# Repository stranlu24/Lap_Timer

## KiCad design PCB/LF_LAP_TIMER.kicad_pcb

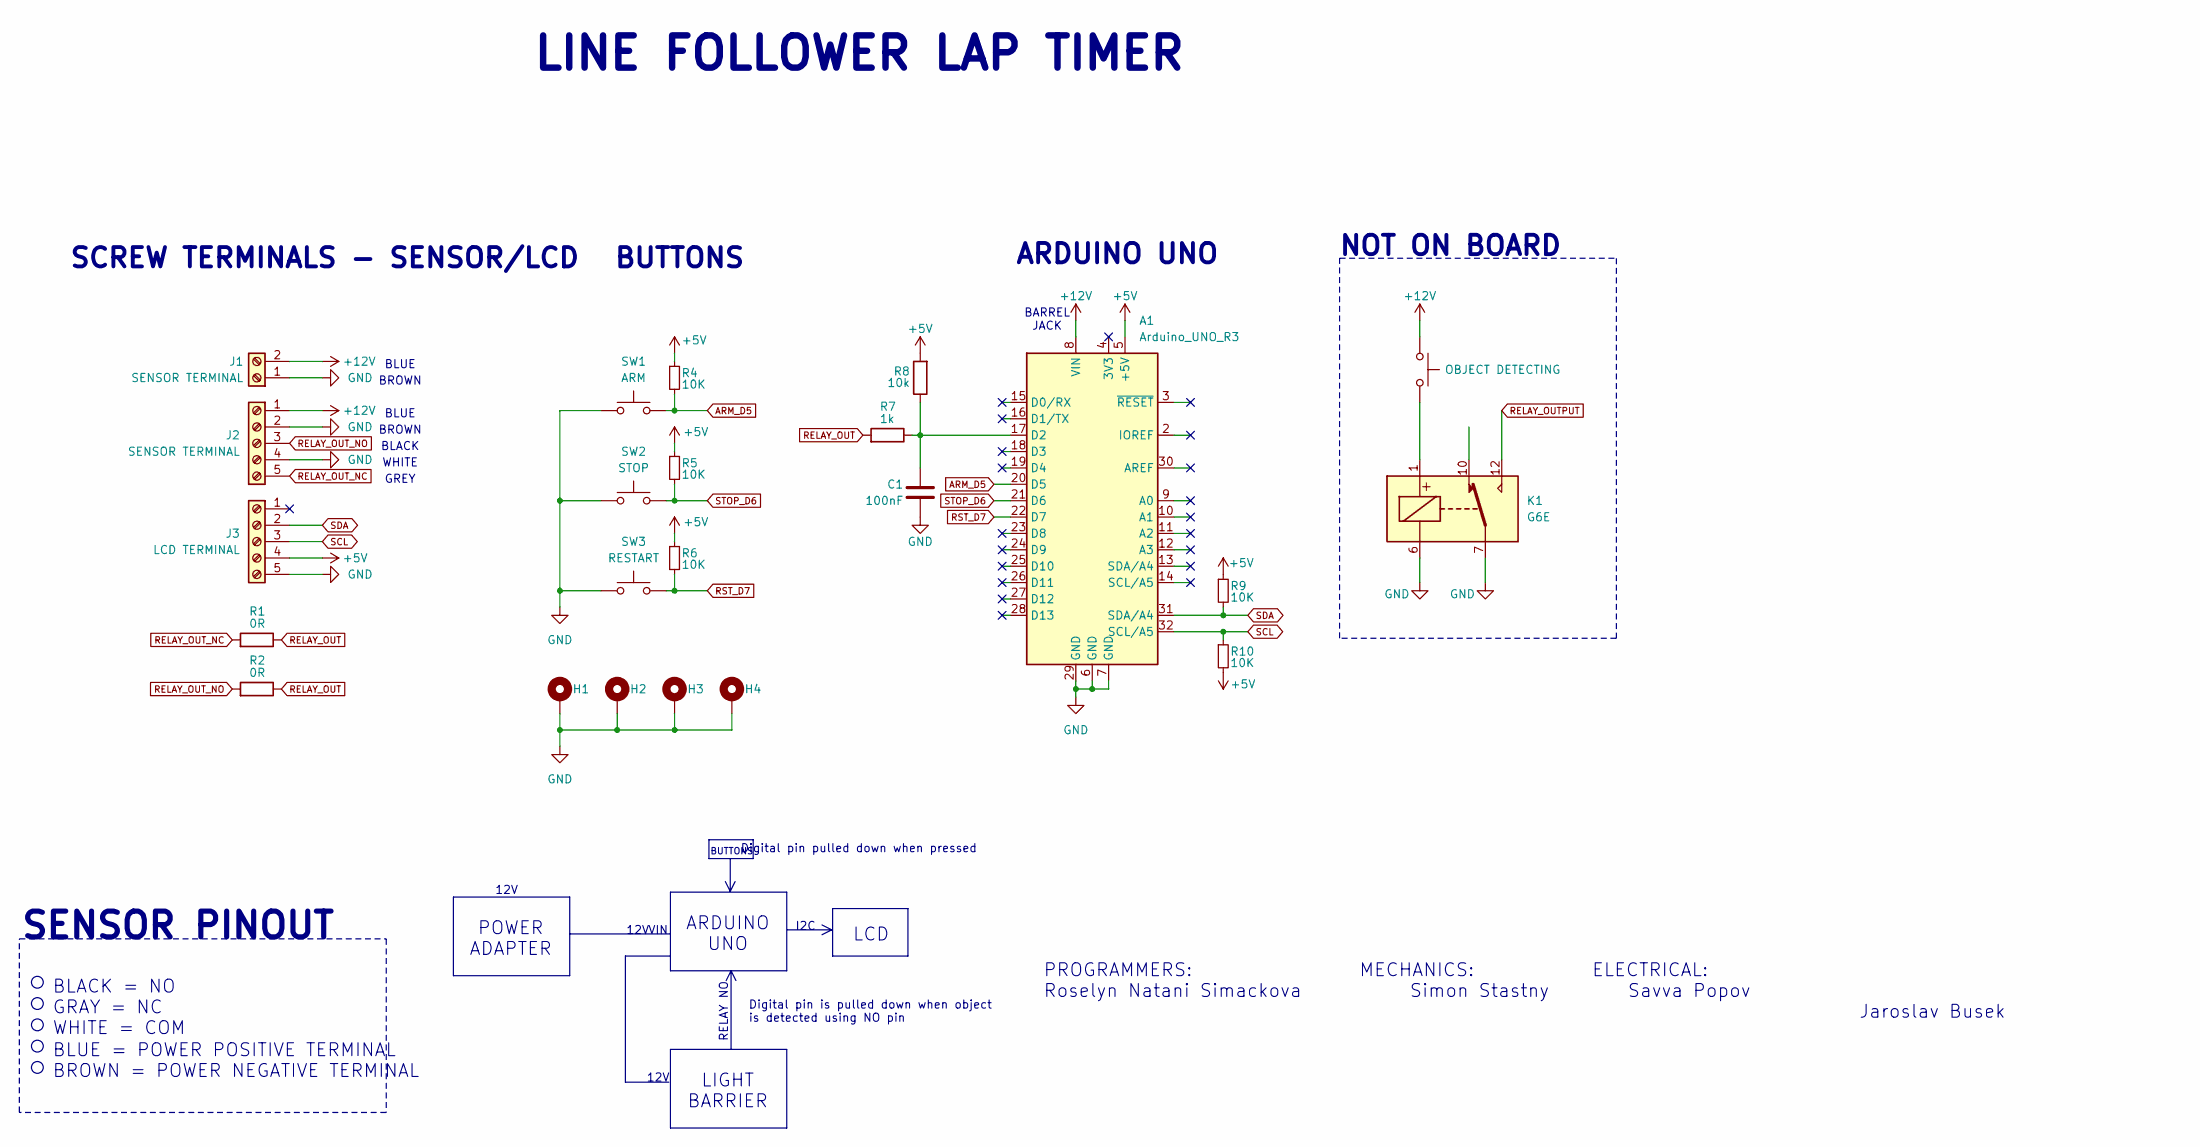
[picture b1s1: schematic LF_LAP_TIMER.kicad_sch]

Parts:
A1: Arduino_UNO_R3
C1: 100nF; C_Disc_D6.0mm_W2.5mm_P5.00mm
H1, H2, H3, H4: MountingHole_Pad; MountingHole_3.2mm_M3_Pad
J1: SENSOR TERMINAL; TerminalBlock_MaiXu_MX126-5.0-02P_1x02_P5.00mm
J2: SENSOR TERMINAL; TerminalBlock_MaiXu_MX126-5.0-05P_1x05_P5.00mm
J3: LCD TERMINAL; TerminalBlock_MaiXu_MX126-5.0-05P_1x05_P5.00mm
K1: G6E
R1, R2: 0R; R_Axial_DIN0207_L6.3mm_D2.5mm_P10.16mm_Horizontal
R4, R5, R6, R9, R10: 10K; R_Axial_DIN0207_L6.3mm_D2.5mm_P10.16mm_Horizontal
R7: 1k; R_Axial_DIN0207_L6.3mm_D2.5mm_P10.16mm_Horizontal
R8: 10k; R_Axial_DIN0207_L6.3mm_D2.5mm_P10.16mm_Horizontal
SW1: ARM; TerminalBlock_MaiXu_MX126-5.0-02P_1x02_P5.00mm
SW2: STOP; TerminalBlock_MaiXu_MX126-5.0-02P_1x02_P5.00mm
SW3: RESTART; TerminalBlock_MaiXu_MX126-5.0-02P_1x02_P5.00mm
SW4: OBJECT DETECTING

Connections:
+5V: A1.5 (+5V), J3.4, R4.1, R5.1, R6.1, R8.2, R9.1, R10.2
+12V: A1.8 (VIN), J1.2, J2.1, SW4.1
ARM_D5: A1.20 (D5), R4.2, SW1.2
GND: A1.6 (GND), A1.7 (GND), A1.29 (GND), C1.2, H1.1, H2.1, H3.1, H4.1, J1.1, J2.2, J2.4, J3.5, K1.6, K1.7, SW1.1, SW2.1, SW3.1
unnamed: A1.17 (D2), C1.1, R7.1, R8.1
unnamed: K1.1, SW4.2
RELAY_OUT: R1.1, R2.1, R7.2
RELAY_OUT_NC: J2.5, R1.2
RELAY_OUT_NO: J2.3, R2.2
RST_D7: A1.22 (D7), R6.2, SW3.2
SCL: A1.32 (SCL/A5), J3.3, R10.1
SDA: A1.31 (SDA/A4), J3.2, R9.2
STOP_D6: A1.21 (D6), R5.2, SW2.2

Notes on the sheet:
BLUE = POWER POSITIVE TERMINAL BROWN = POWER NEGATIVE TERMINAL
ARDUINO UNO
BROWN
BUTTONS
12V
SCREW TERMINALS - SENSOR/LCD
VIN
I2C
SENSOR PINOUT
BARREL JACK
RELAY NO
BLUE
WHITE
LIGHT BARRIER
BLACK
GREY
ARDUINO UNO
LINE FOLLOWER LAP TIMER
LCD
BLACK = NO GRAY = NC WHITE = COM
POWER ADAPTER
NOT ON BOARD
Digital pin pulled down when pressed
PROGRAMMERS: MECHANICS: ELECTRICAL: Roselyn Natani Simackova Simon Stastny Savva Popov Jaroslav Busek
Digital pin is pulled down when object is detected using NO pin

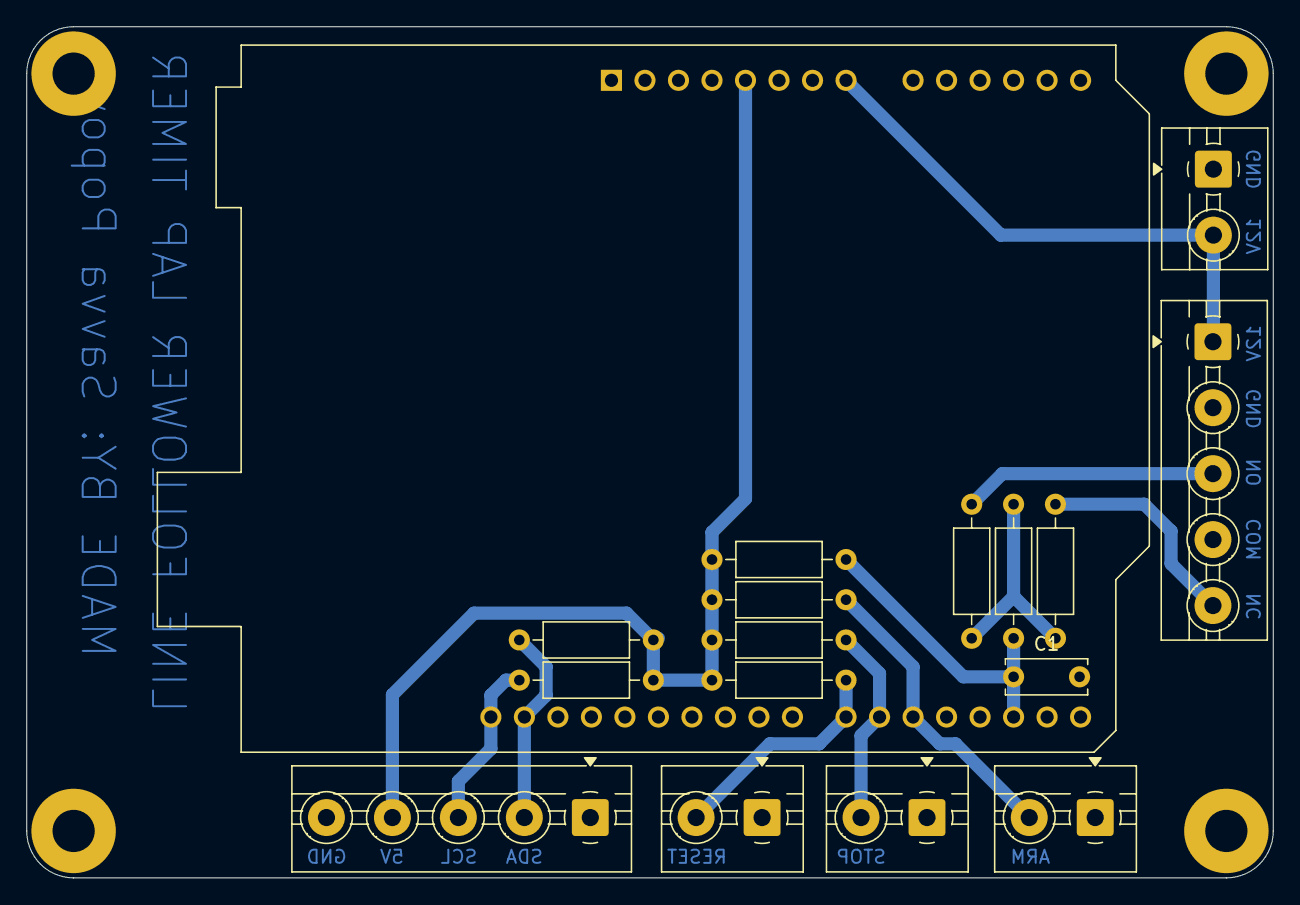
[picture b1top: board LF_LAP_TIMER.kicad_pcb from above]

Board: 2 copper layers, 94.5 x 64.5 mm, 21 parts (0 on the bottom side), 12 nets.
